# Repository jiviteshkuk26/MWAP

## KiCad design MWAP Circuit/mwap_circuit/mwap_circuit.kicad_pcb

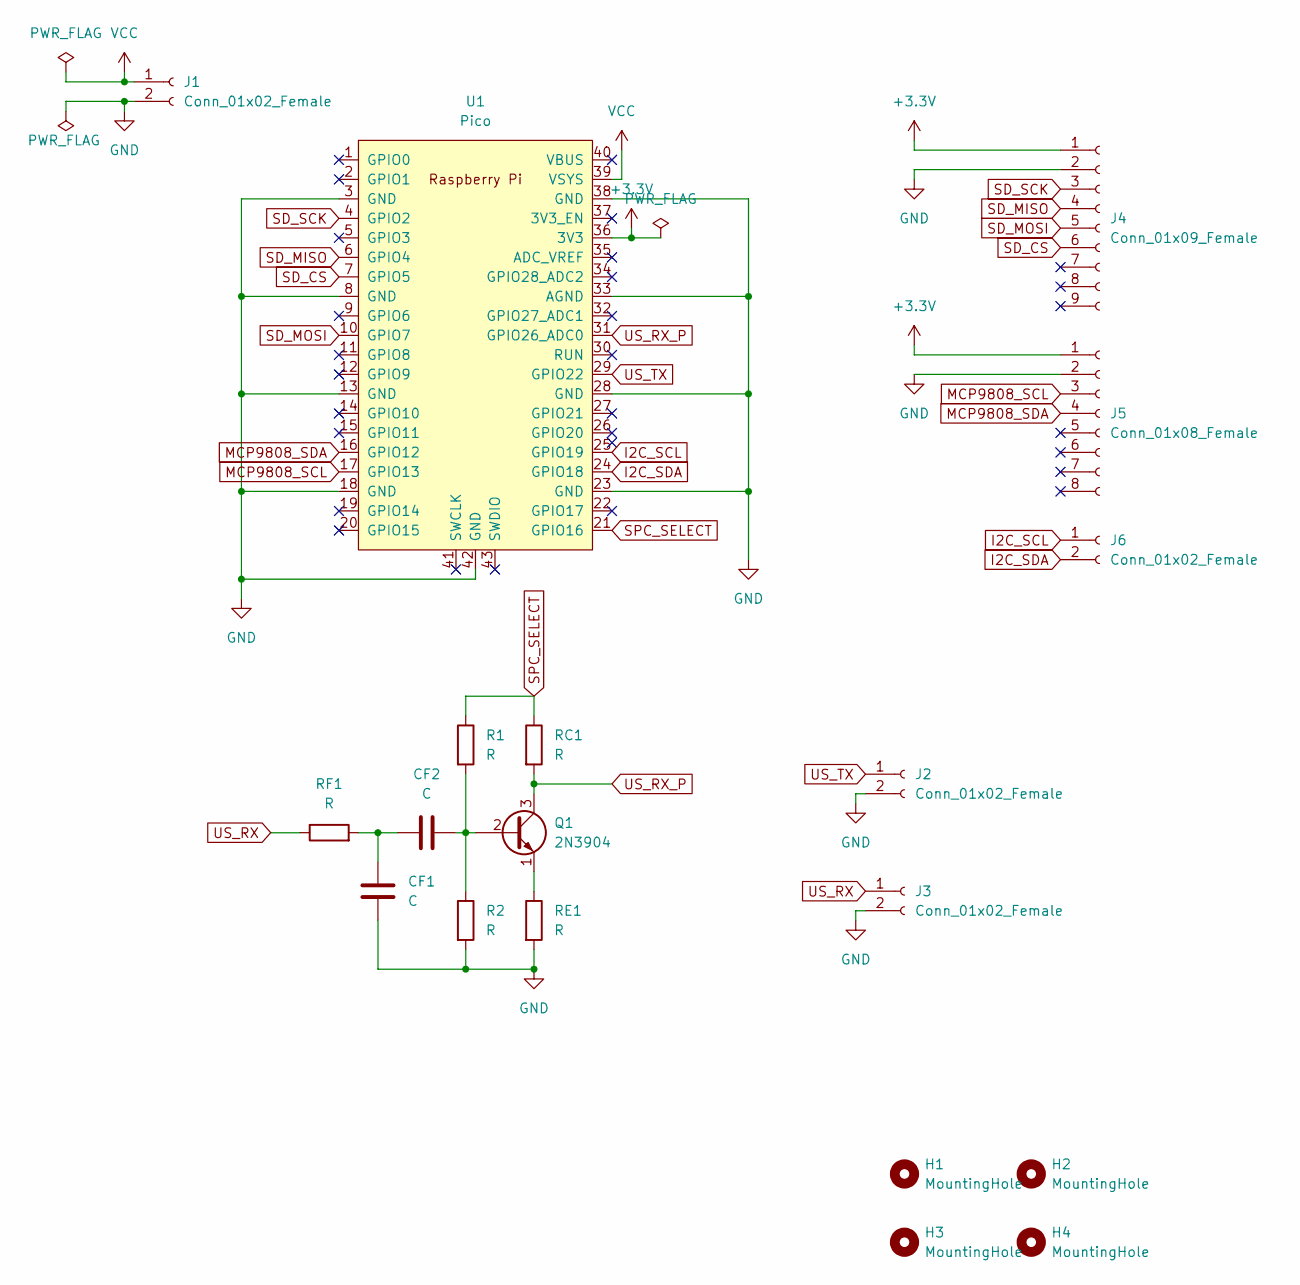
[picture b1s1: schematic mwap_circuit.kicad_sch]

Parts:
CF1, CF2: C; C_Disc_D4.7mm_W2.5mm_P5.00mm
H1, H2, H3, H4: MountingHole; MountingHole_2.7mm_M2.5
J1, J2, J3, J6: Conn_01x02_Female; JST_PH_S2B-PH-K_1x02_P2.00mm_Horizontal
J4: Conn_01x09_Female; PinHeader_1x09_P2.54mm_Vertical
J5: Conn_01x08_Female; PinHeader_1x08_P2.54mm_Vertical
Q1: 2N3904; TO-92_Inline
R1, R2: R; R_Axial_DIN0411_L9.9mm_D3.6mm_P15.24mm_Horizontal
RC1: R; R_Axial_DIN0411_L9.9mm_D3.6mm_P15.24mm_Horizontal
RE1: R; R_Axial_DIN0411_L9.9mm_D3.6mm_P15.24mm_Horizontal
RF1: R; R_Axial_DIN0411_L9.9mm_D3.6mm_P15.24mm_Horizontal
U1: Pico; RPi_Pico_SMD_TH

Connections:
+3.3V: J4.1, J5.1, U1.36 (3V3)
GND: CF1.2, J1.2, J2.2, J3.2, J4.2, J5.2, R2.2, RE1.2, U1.3 (GND), U1.8 (GND), U1.13 (GND), U1.18 (GND), U1.23 (GND), U1.28 (GND), U1.33 (AGND), U1.38 (GND), U1.42 (GND)
I2C_SCL: J6.1, U1.25 (GPIO19)
I2C_SDA: J6.2, U1.24 (GPIO18)
MCP9808_SCL: J5.3, U1.17 (GPIO13)
MCP9808_SDA: J5.4, U1.16 (GPIO12)
unnamed: CF1.1, CF2.1, RF1.2
unnamed: CF2.2, Q1.2 (B), R1.2, R2.1
unnamed: Q1.1 (E), RE1.1
SD_CS: J4.6, U1.7 (GPIO5)
SD_MISO: J4.4, U1.6 (GPIO4)
SD_MOSI: J4.5, U1.10 (GPIO7)
SD_SCK: J4.3, U1.4 (GPIO2)
SPC_SELECT: R1.1, RC1.1, U1.21 (GPIO16)
US_RX: J3.1, RF1.1
US_RX_P: Q1.3 (C), RC1.2, U1.31 (GPIO26_ADC0)
US_TX: J2.1, U1.29 (GPIO22)
VCC: J1.1, U1.39 (VSYS)

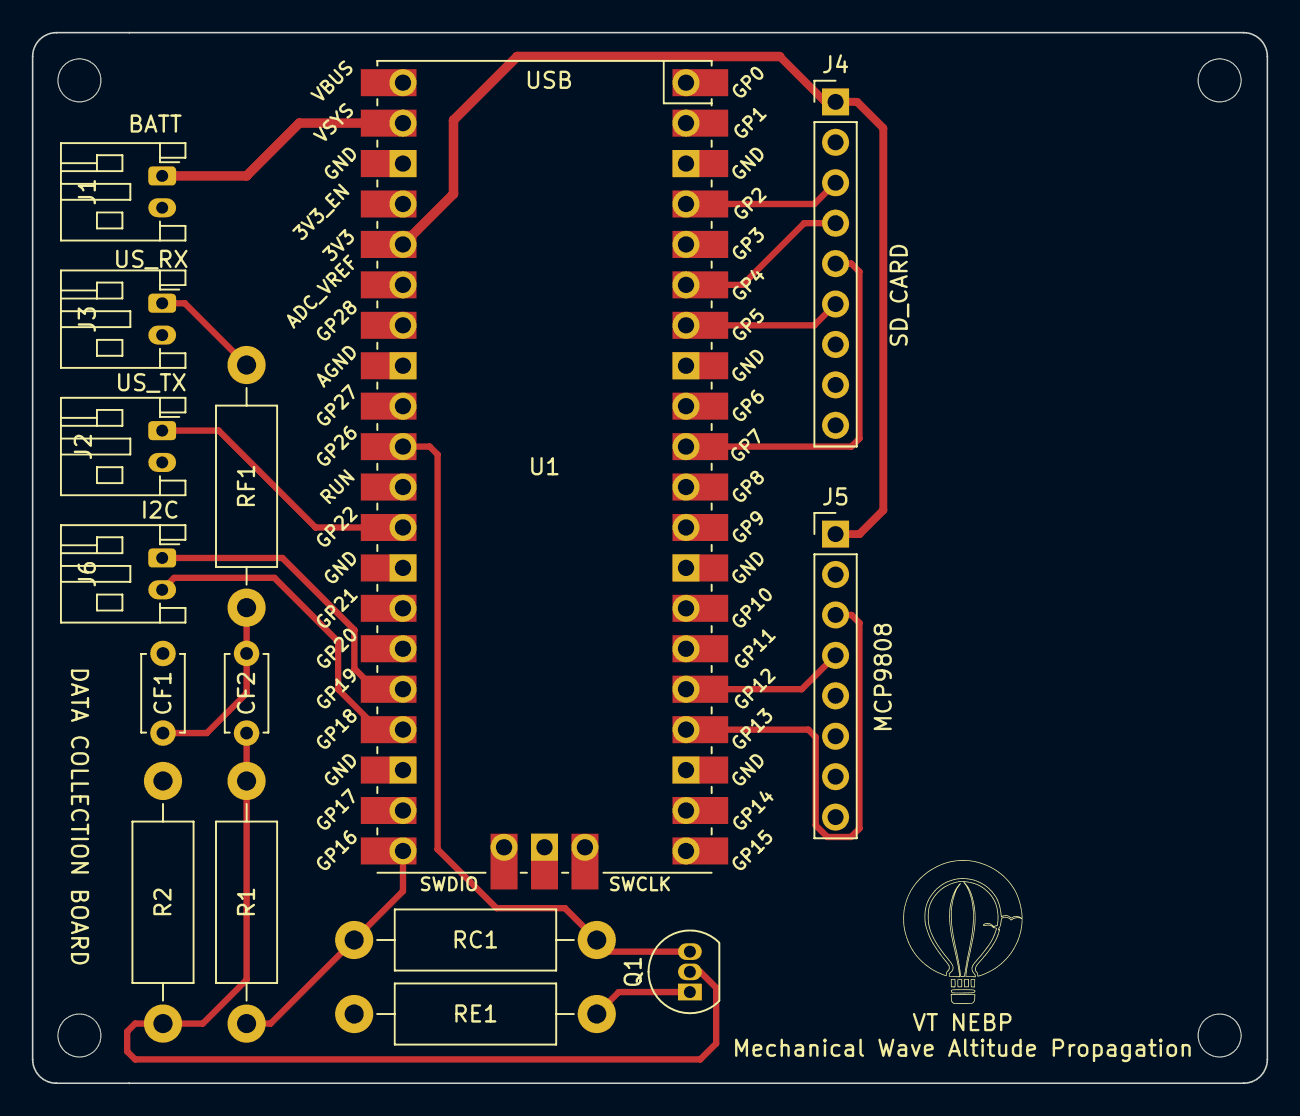
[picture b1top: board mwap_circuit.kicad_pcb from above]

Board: 2 copper layers, 77.6 x 66.0 mm, 19 parts (0 on the bottom side), 18 nets.

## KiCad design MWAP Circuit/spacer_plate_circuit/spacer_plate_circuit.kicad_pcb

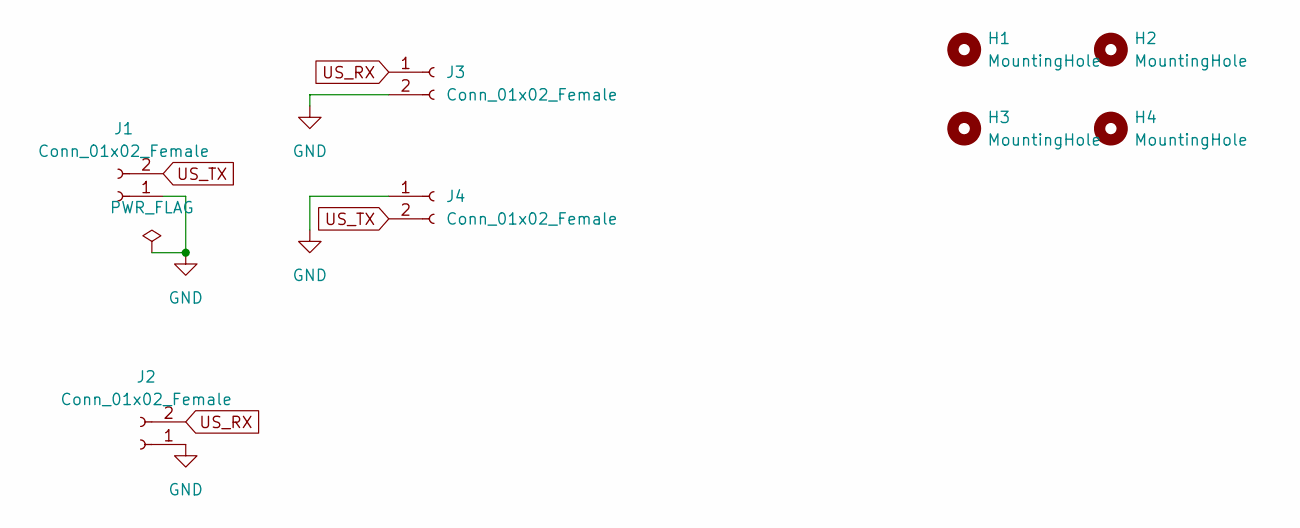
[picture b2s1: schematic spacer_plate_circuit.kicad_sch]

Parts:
H1, H2, H3, H4: MountingHole; MountingHole_2.7mm_M2.5
J1, J2: Conn_01x02_Female; JST_PH_S2B-PH-K_1x02_P2.00mm_Horizontal
J3, J4: Conn_01x02_Female; PinSocket_1x02_P2.54mm_Vertical

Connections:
GND: J1.1, J2.1, J3.2, J4.1
US_RX: J2.2, J3.1
US_TX: J1.2, J4.2

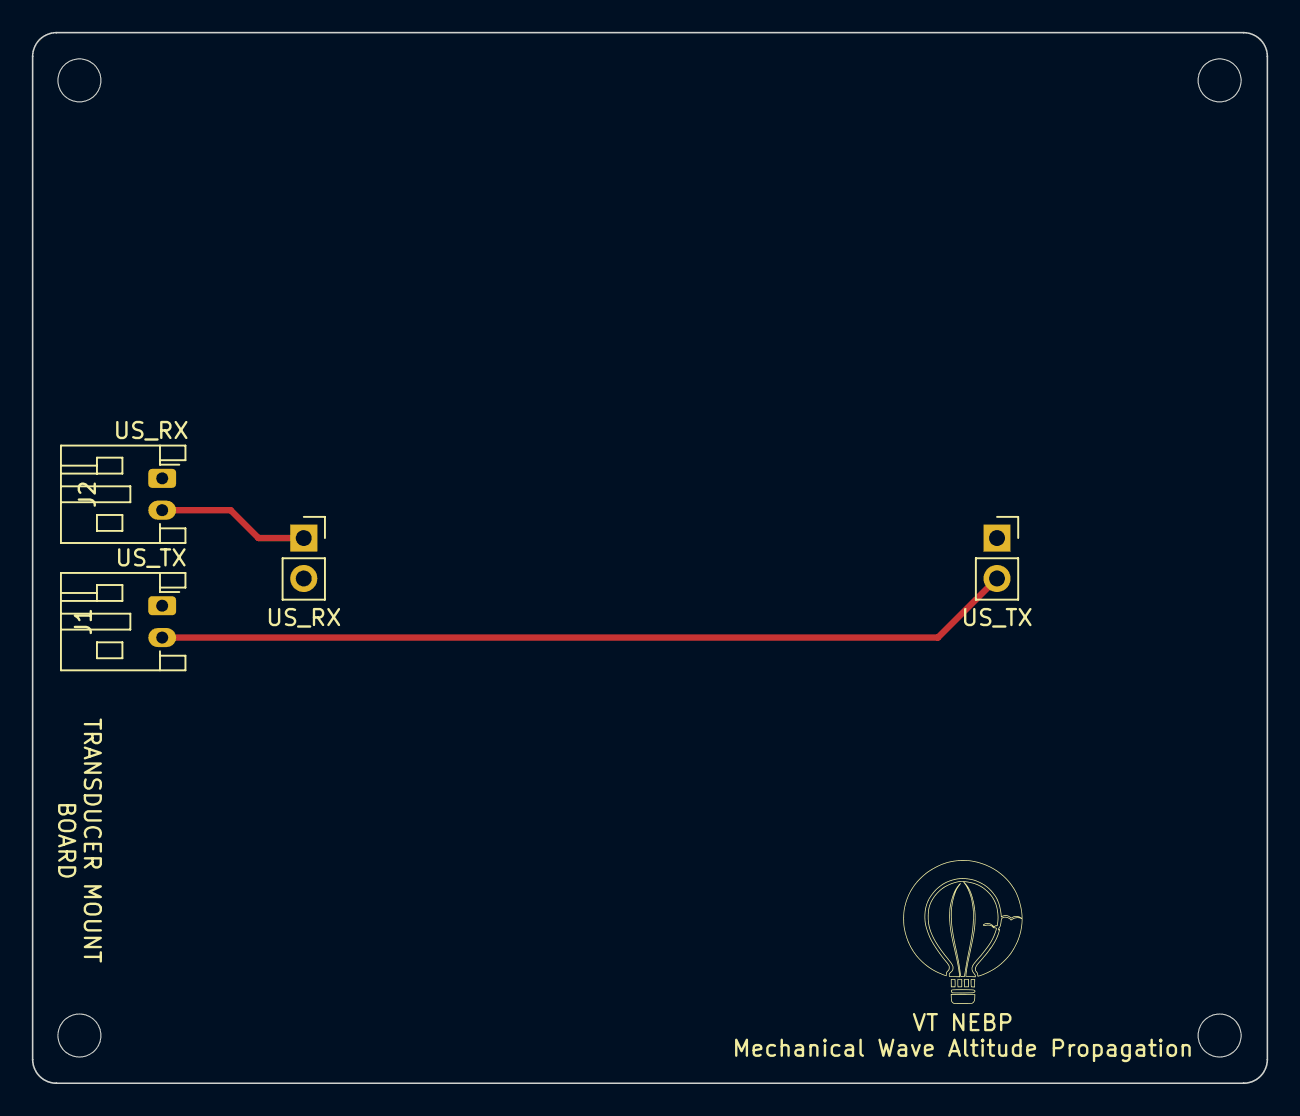
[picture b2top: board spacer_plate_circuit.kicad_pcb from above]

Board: 2 copper layers, 77.6 x 66.0 mm, 8 parts (0 on the bottom side), 3 nets.

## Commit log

2024-05-16 Circuit Files
